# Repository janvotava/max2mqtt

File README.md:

# MAX2MQTT

Replaces the eQ-3 MAX! Cube: an ESP32 with a CC1101 runs your MAX! thermostats, fires the gas furnace when a room
needs heat, and talks to Home Assistant over MQTT. Everything is set up in its web UI.

Runs on D1-mini-sized ESP32 boards (HW-665 / ESP32-WROOM-32, Lolin C3 Mini) with a CC1101 shield
([`hardware/cc1101-shield`](hardware/cc1101-shield)) and a relay shield that switches the furnace.

The firmware is Rust/Embassy, in [`docs/development.md`](docs/development.md): hardware, pin mapping, build and flash instructions,
and how it differs from the earlier C++ firmware for the Wemos D1 mini (in the git history).

Radio silent on a new board? See [hardware/cc1101-shield/troubleshooting.md](hardware/cc1101-shield/troubleshooting.md) for soldering faults and the
per-module frequency correction.

## Usage

```bash
git clone git@github.com:janvotava/max2mqtt.git
cd max2mqtt
direnv allow        # or: devenv shell
fw-flash            # build the web UI and the firmware, flash over USB, monitor
```

## Setup

The serial console prints the device password at every boot (lost it, or want a factory reset over USB? see
[docs/development.md](docs/development.md#lost-password-factory-reset)). Then:

1. **Wi-Fi.** Without a configured network (or when the board cannot join it for a minute) it opens a hotspot
   `max2mqtt-XXXX` with that password. Phones open the setup page by themselves; otherwise go to
   http://192.168.4.1/. Pick the network under Settings and save; the board restarts and joins it.
2. **Web UI.** On the home network, at the address printed on the console (or `http://max/`). Settings for Wi-Fi,
   MQTT (broker, topic prefix, Home Assistant discovery), hostname, password, and the CC1101 frequency
   correction; an overview of the furnace and rooms; the devices with pairing, names, rooms and temperatures;
   the radio address, time zone and frequency correction (measured from the thermostats' packets); a live log;
   firmware updates (`fw-image` builds the file to upload).
3. **Home Assistant.** With an MQTT broker set and discovery on (the default), every device with a room shows up
   as a thermostat, window sensor and so on, with the bridge's furnace and pairing switch.

Optional build-time defaults for the first boot (Wi-Fi, MQTT, password) can go in
`esp/secrets.toml`, see `secrets.example.toml`.

## MQTT

MQTT is for Home Assistant: device state, and the commands its thermostat cards send (temperature, mode).
Rooms, week programs, names and heating settings are set in the web UI, so whatever can publish to the broker
cannot reconfigure the bridge. Topics: [docs/development.md](docs/development.md#mqtt-and-home-assistant).

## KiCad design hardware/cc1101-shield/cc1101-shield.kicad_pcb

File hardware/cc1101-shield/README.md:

# CC1101 shield

A CC1101 868 MHz radio module on a shield for D1-mini-sized boards (HW-665 / ESP32-WROOM-32, Lolin C3 Mini).

| Top | Bottom |
|---|---|
|  |  |

To order it, upload [`fab/cc1101-shield-gerbers.zip`](fab/cc1101-shield-gerbers.zip) to a PCB maker (2 layers,
1.6 mm, anything standard). The schematic is [`fab/cc1101-shield-schematic.pdf`](fab/cc1101-shield-schematic.pdf).

| Module pin | | D1 mini | ESP32 (HW-665) |
|---|---|---|---|
| 1 VCC | 3.3 V | 3V3 | |
| 2 GND | | GND | |
| 3 MOSI | | D7 | GPIO23 |
| 4 SCLK | | D5 | GPIO18 |
| 5 MISO | | D6 | GPIO19 |
| 6 GDO2 | packet received | D2 | GPIO21 |
| 7 GDO0 | not connected | | |
| 8 CSN | chip select | D8 | GPIO5 |

The pins are as the firmware expects them (`esp/src/board.rs`).

## v2

Same outline and hole positions as v1, so it fits the same boards and modules. Changed, from the notes in
[troubleshooting.md](troubleshooting.md):

- 3V3 and GND reach the module as 0.6 mm tracks. On v1 they were copper fills only, which pulled the heat away
  from the iron: those four joints were the ones that failed.
- The module's 2 mm header has 1.6 mm pads around 0.9 mm holes (v1: 1.2 mm around 0.81 mm, a 0.19 mm ring).
- GDO0 is not connected. On v1 it went to D3, which is GPIO0 on the D1 mini and must be high at boot, while the
  CC1101 puts a clock on it after reset.
- Ground fill on both sides, stitched with vias.
- Tracks run between the pin rows, so the pin labels stay readable; the module's pin names are on the bottom,
  next to the joints.

Still true of v2: GDO2 (D2) is GPIO8 on the C3 Mini, a strapping pin, so flash a C3 the first time with the
shield unplugged. Keep the module's coil antenna away from the board's Wi-Fi antenna.

v2 has not been made yet. v1 as built is in [`v1/`](v1): its Gerbers and the EasyEDA Pro project.

## Changing it

The board is written by [`generate.py`](generate.py): the parts, every track and the outline are in that one
script. Edit it and run `./build.sh` (KiCad 10), which regenerates the KiCad files, fails unless KiCad's
electrical and design rule checks are clean (including that the board matches the schematic), and exports the
Gerbers, the schematic PDF and the pictures. Opening the `.kicad_pro` in KiCad works too, but the next
`./build.sh` overwrites hand edits.

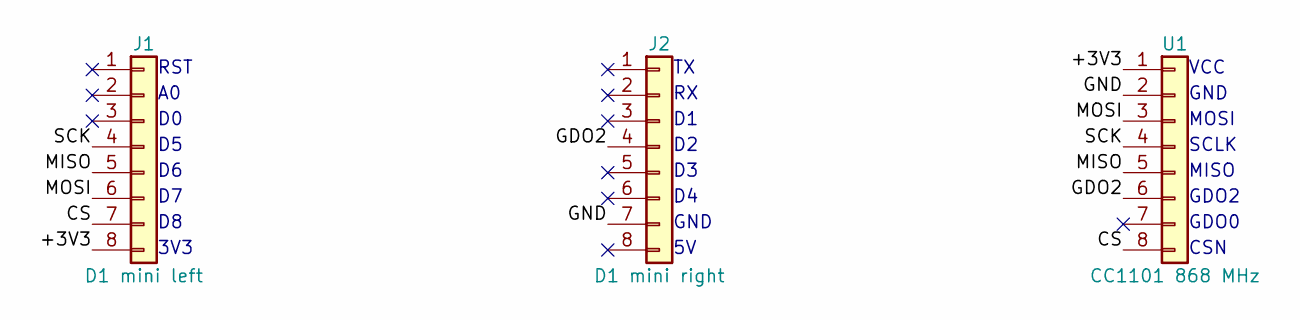
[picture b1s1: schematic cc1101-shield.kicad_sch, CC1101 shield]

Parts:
J1: D1 mini left; PinHeader_1x08_P2.54mm_Vertical
J2: D1 mini right; PinHeader_1x08_P2.54mm_Vertical
U1: CC1101 868 MHz; CC1101_Module_1x08_P2.00mm

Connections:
/+3V3: J1.8, U1.1
/CS: J1.7, U1.8
/GDO2: J2.4, U1.6
/GND: J2.7, U1.2
/MISO: J1.5, U1.5
/MOSI: J1.6, U1.3
/SCK: J1.4, U1.4

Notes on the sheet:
RST
3V3
GND
VCC
MOSI
SCLK
MISO
GDO2
GDO0
CSN

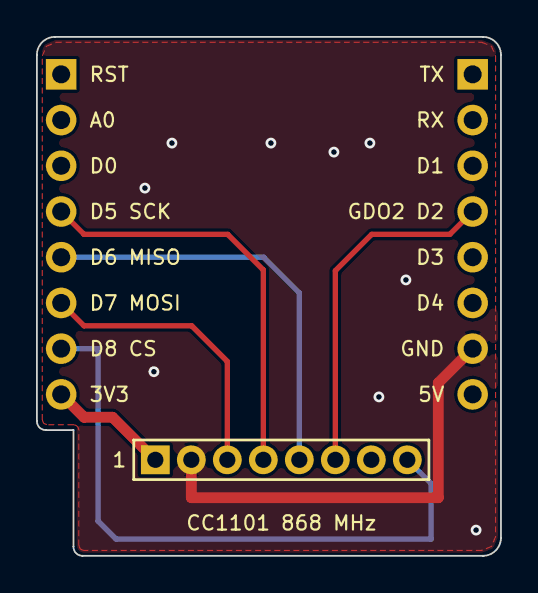
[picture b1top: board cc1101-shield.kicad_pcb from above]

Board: 2 copper layers, 25.8 x 28.8 mm, 3 parts (0 on the bottom side), 7 nets.

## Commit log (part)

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2024-11-27 fix: unitialized for loop variables
2024-11-27 style: code format
2024-11-27 chore: some MQTT debug info
